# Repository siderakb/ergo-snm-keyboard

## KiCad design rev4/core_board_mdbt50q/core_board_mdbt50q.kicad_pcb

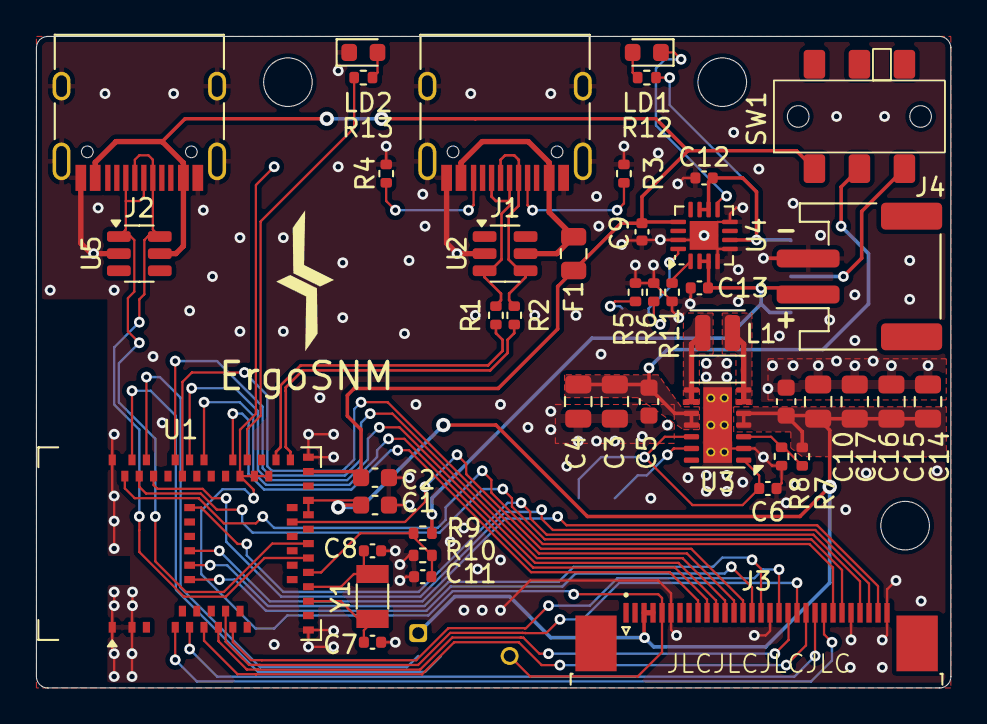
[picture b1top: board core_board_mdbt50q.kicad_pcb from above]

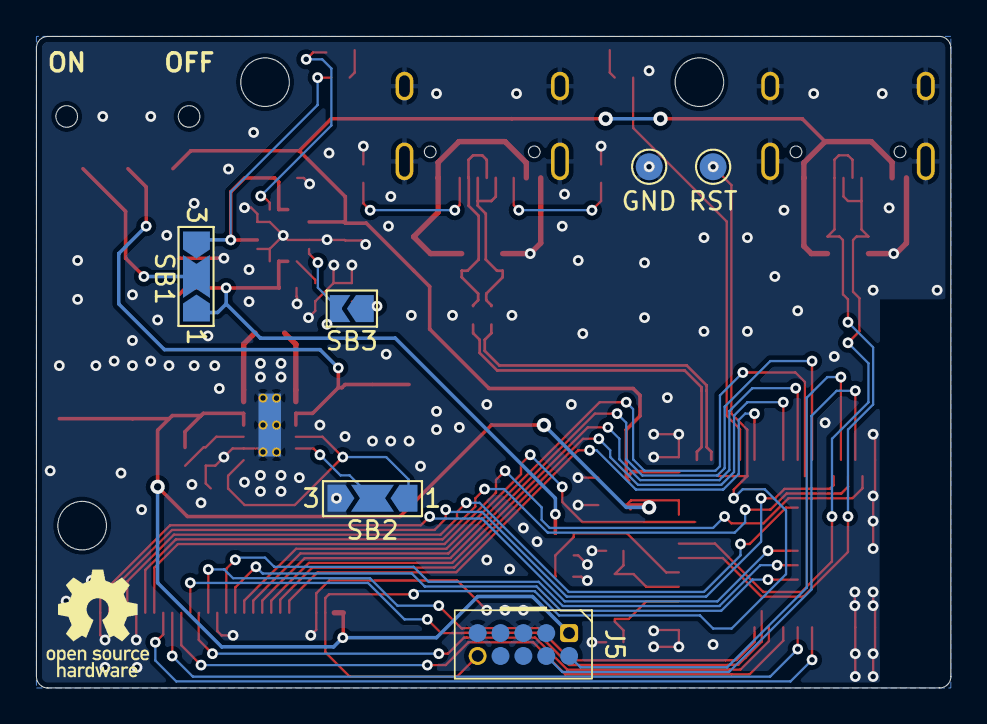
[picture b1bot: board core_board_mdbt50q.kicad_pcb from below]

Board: 2 copper layers, 50.8 x 36.2 mm, 54 parts (6 on the bottom side), 53 nets.

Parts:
C1, C2: 10uF; C_0603_1608Metric
C3, C4, C14, C15, C16, C17: 22uF; C_0805_2012Metric
C5, C10: 2.2uF; C_0603_1608Metric
C6, C11: 100nF; C_0402_1005Metric
C7, C8: 12pF; C_0402_1005Metric
C9: 1uF; C_0402_1005Metric
C12, C13: 4.7uF; C_0402_1005Metric
F1: 500mA, 6V; Fuse_0805_2012Metric
H1, H2, H3: MountingHole; MountingHole_2.7mm_M2.5_ISO7380
J1, J2: USB_C_Receptacle_USB2.0; USB_C_Receptacle_HRO_TYPE-C-31-M-12
J3: Conn_01x30; TE_3-1734839-0_1x30-1MP_P0.5mm_Horizontal
J4: Conn_Batt; JST_PH_S2B-PH-SM4-TB_1x02-1MP_P2.00mm_Horizontal
J5: Debug; SWD 10pin
L1: 1.5uH; L_Changjiang_FNR252012S
LD1: RED; LED_0603_1608Metric
LD2: BLUE; LED_0603_1608Metric
R1, R2: 27R; R_0402_1005Metric
R3, R4: 5.1k; R_0402_1005Metric
R5: 2k; R_0402_1005Metric
R6, R11, R12, R13: 10k; R_0402_1005Metric
R7: 1M; R_0402_1005Metric
R8: 180k; R_0402_1005Metric
R9: 820k; R_0402_1005Metric
R10: 2M; R_0402_1005Metric
SB1: Vsrc Select; SolderJumper-3_P2.0mm_Open_TrianglePad1.0x1.5mm_NumberLabels
SB2: Power Save; SolderJumper-3_P2.0mm_Open_TrianglePad1.0x1.5mm_NumberLabels
SB3: Charge Boost; SolderJumper-2_P1.3mm_Open_TrianglePad1.0x1.5mm
SW1: SW_DPDT_x2; MSKT-22D14-T
TP1: RST; TestPoint_Pad_D1.5mm
TP2: GND; TestPoint_Pad_D1.5mm
U1: MDBT50Q-1MV2; Raytac_MDBT50Q
U2, U5: SRV05-4; SOT-23-6
U3: TPS63020; VSON-14-1EP_3x4.45mm_P0.65mm_EP1.6x4.2mm_ThermalVias
U4: BQ24075RGT; VQFN-16-1EP_3x3mm_P0.5mm_EP1.6x1.6mm
Y1: 32.768kHz; Crystal_SMD_3215-2Pin_3.2x1.5mm

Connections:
+5V: F1.1, J1.A4 (VBUS), J1.A9 (VBUS), J1.B4 (VBUS), J1.B9 (VBUS), U2.5 (VP)
+BATT: C13.2, J4.1, R9.1, SB1.1 (A), U4.2 (BAT), U4.3 (BAT)
/MCU_D+: R2.2, U1.35 (D+)
/MCU_D-: R1.1, U1.34 (D-)
/PWR_SAVE: SB2.2 (C), U3.13 (PS/SYNC)
/VINA: C6.1, SB2.1 (A), U3.1 (VINA), U3.12 (EN)
GND: C1.2, C2.1, C3.2, C4.2, C5.2, C6.2, C7.1, C8.1, C9.2, C10.2, C11.2, C12.1, C13.1, C14.2, C15.2, C16.2, C17.2, J1.A1 (GND), J1.A12 (GND), J1.B1 (GND), J1.B12 (GND), J1.S1 (SHIELD), J2.A1 (GND), J2.A12 (GND), J2.B1 (GND), J2.B12 (GND), J2.S1 (SHIELD), J3.6, J3.17, J3.26, J3.30, J4.2, J5.3, J5.5, J5.9, LD2.1 (K), R3.2, R4.2, R5.2, R6.2, R8.2, R10.2, R11.1, SB2.3 (B), TP2.1, U1.1 (GND), U1.2 (GND), U1.15 (GND), U1.33 (GND), U1.55 (GND), U2.2 (VN), U3.2 (GND), U3.15 (PAD), U4.4 (~CE), U4.5 (EN2), U4.8 (VSS), U4.15 (SYSOFF), U4.17 (VSS), U5.2 (VN)
unnamed: J1.A5 (CC1), R3.1
unnamed: J1.B5 (CC2), R4.1
unnamed: L1.1, U3.8 (L1), U3.9 (L1)
unnamed: L1.2, U3.6 (L2), U3.7 (L2)
unnamed: LD1.2 (A), R12.2
unnamed: LD1.1 (K), U4.9 (~CHG)
unnamed: LD2.2 (A), R13.2
unnamed: SB1.2 (C), SW1.1 (A)
unnamed: R5.1, SB3.1 (A)
unnamed: R6.1, SB3.2 (B), U4.16 (ISET)
unnamed: C3.1, C4.1, C5.1, SW1.2 (B), U3.10 (VIN), U3.11 (VIN)
unnamed: R7.2, R8.1, U3.3 (FB)
unnamed: R11.2, U4.1 (TS)
P0.02: J3.20, U1.11 (P0.02)
P0.04: C11.1, R9.2, R10.1, U1.20 (P0.04)
P0.06: J2.A7 (D-), J2.B7 (D-), U1.22 (P0.06), U5.6 (IO4)
P0.08: J2.A6 (D+), J2.B6 (D+), U1.24 (P0.08), U5.1 (IO1)
P0.09: J3.25, U1.52 (P0.09)
P0.10: J3.24, U1.54 (P0.10)
P0.11: J3.14, U1.27 (P0.11)
P0.15: R13.1, U1.39 (P0.15)
P0.17: J3.9, U1.41 (P0.17)
P0.20: J3.10, U1.44 (P0.20)
P0.22: J3.11, U1.46 (P0.22)
P0.24: J3.12, U1.48 (P0.24)
P0.29: J3.19, U1.10 (P0.29)
P0.31: J3.18, U1.12 (P0.31)
P1.00: J3.13, U1.47 (P1.00)
P1.01: J3.27, U1.61 (P1.01)
P1.02: J3.28, U1.50 (P1.02)
P1.04: J3.15, U1.56 (P1.04)
P1.06: J3.16, U1.57 (P1.06)
P1.07: J3.29, U1.58 (P1.07)
P1.11: J3.23, U1.4 (P1.11)
P1.13: J3.22, U1.6 (P1.13)
P1.15: J3.21, U1.8 (P1.15)
RESET: J3.5, J5.10, TP1.1, U1.36 (P0.14), U1.38 (P0.16), U1.40 (P0.18)
SWC: J5.4, U1.53 (SWDCLK)
SWD: J5.2, U1.51 (SWDIO)
USB_D+: J1.A6 (D+), J1.B6 (D+), R2.1, U2.3 (IO2)
USB_D-: J1.A7 (D-), J1.B7 (D-), R1.2, U2.4 (IO3)
VBUS: C2.2, C9.1, F1.2, J2.A4 (VBUS), J2.A9 (VBUS), J2.B4 (VBUS), J2.B9 (VBUS), SW1.3 (C), U1.32 (VBUS), U4.13 (IN), U5.5 (VP)
VDD: C1.1, C10.1, C14.1, C15.1, C16.1, C17.1, J3.3, J3.4, J5.1, R7.1, U1.28 (VDD), U1.30 (VDDH), U3.4 (VOUT), U3.5 (VOUT)
VDDH: C12.2, R12.1, SB1.3 (B), U4.6 (EN1), U4.10 (OUT), U4.11 (OUT)
XL1: C7.2, U1.17 (P0.00), Y1.2
XL2: C8.2, U1.18 (P0.01), Y1.1

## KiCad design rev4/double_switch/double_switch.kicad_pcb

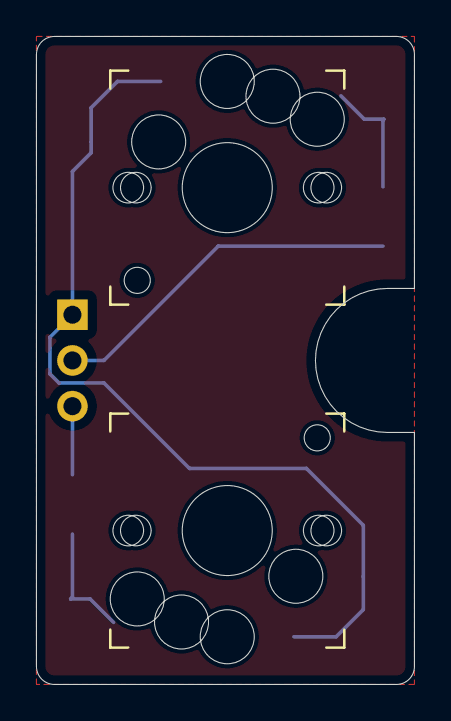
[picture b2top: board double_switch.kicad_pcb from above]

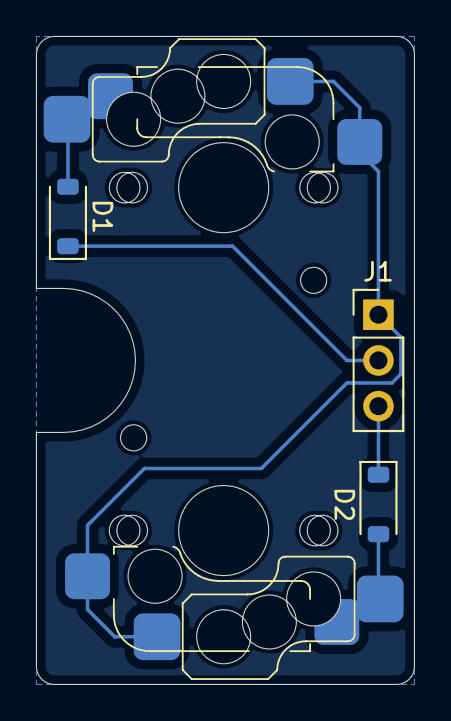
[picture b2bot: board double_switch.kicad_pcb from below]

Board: 2 copper layers, 21.0 x 36.0 mm, 5 parts (3 on the bottom side), 5 nets.

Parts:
D1, D2: 1N4148; D_SOD-123
J1: Conn_01x03; PinHeader_1x03_P2.54mm_Vertical
SW1, SW2: SW_Push_45deg; SW_MX_Kailh_Choc_V1V2_HotSwap_Hybrid_alt1

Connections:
COL0: J1.1, SW1.1, SW2.1
unnamed: D1.2 (A), SW1.2
unnamed: D2.2 (A), SW2.2
ROW0: D1.1 (K), J1.2
ROW1: D2.1 (K), J1.3

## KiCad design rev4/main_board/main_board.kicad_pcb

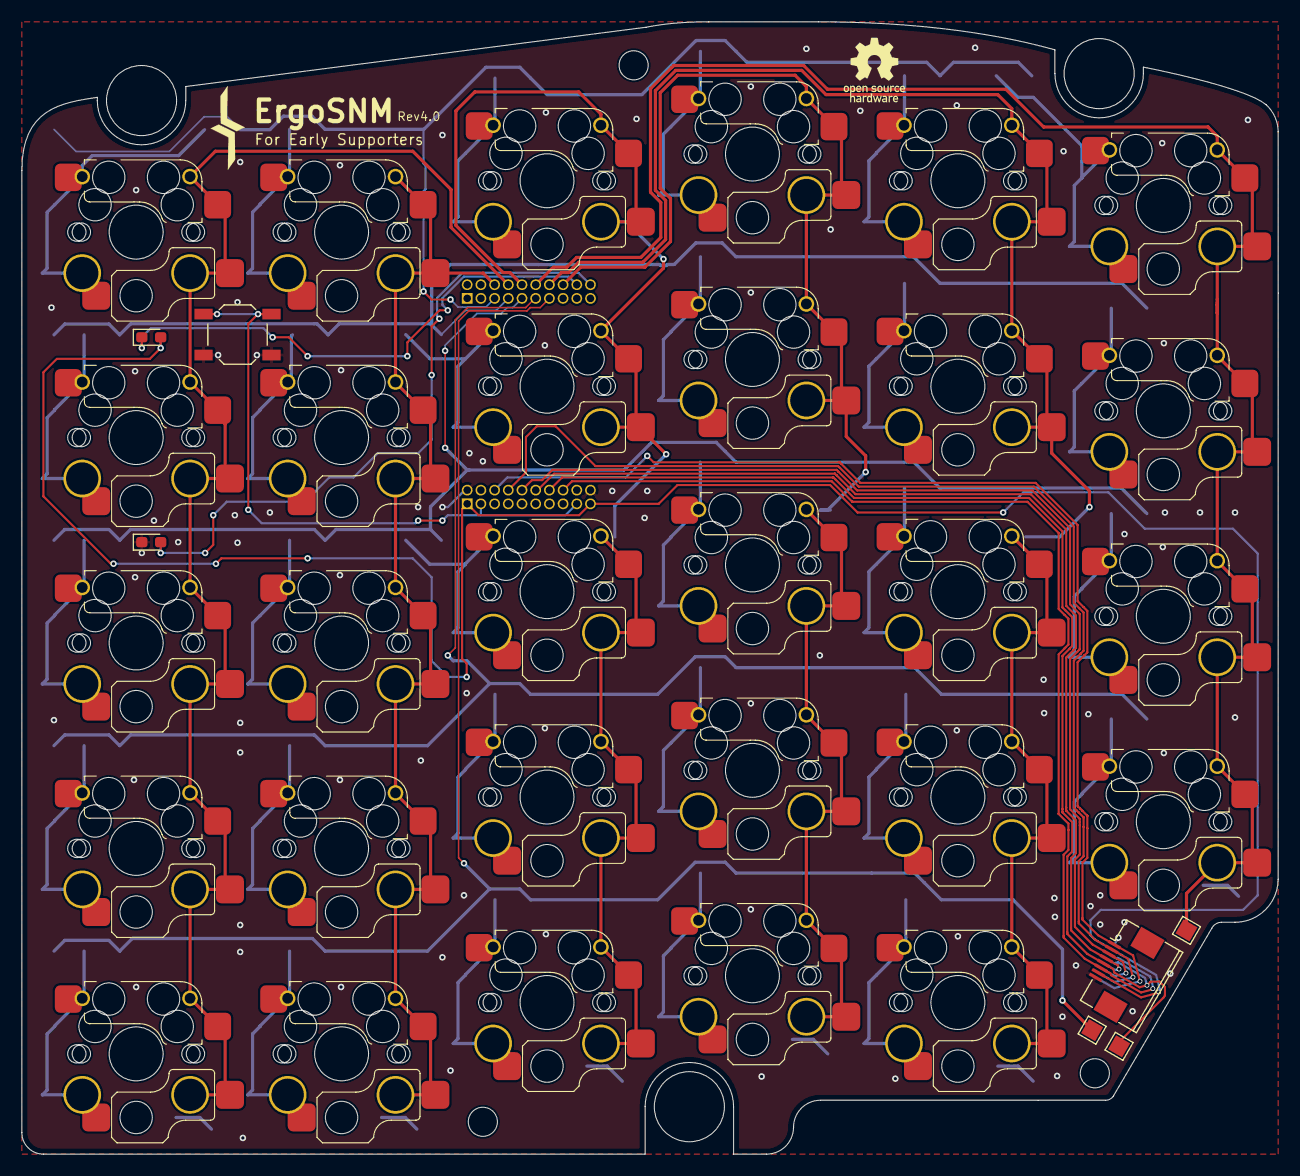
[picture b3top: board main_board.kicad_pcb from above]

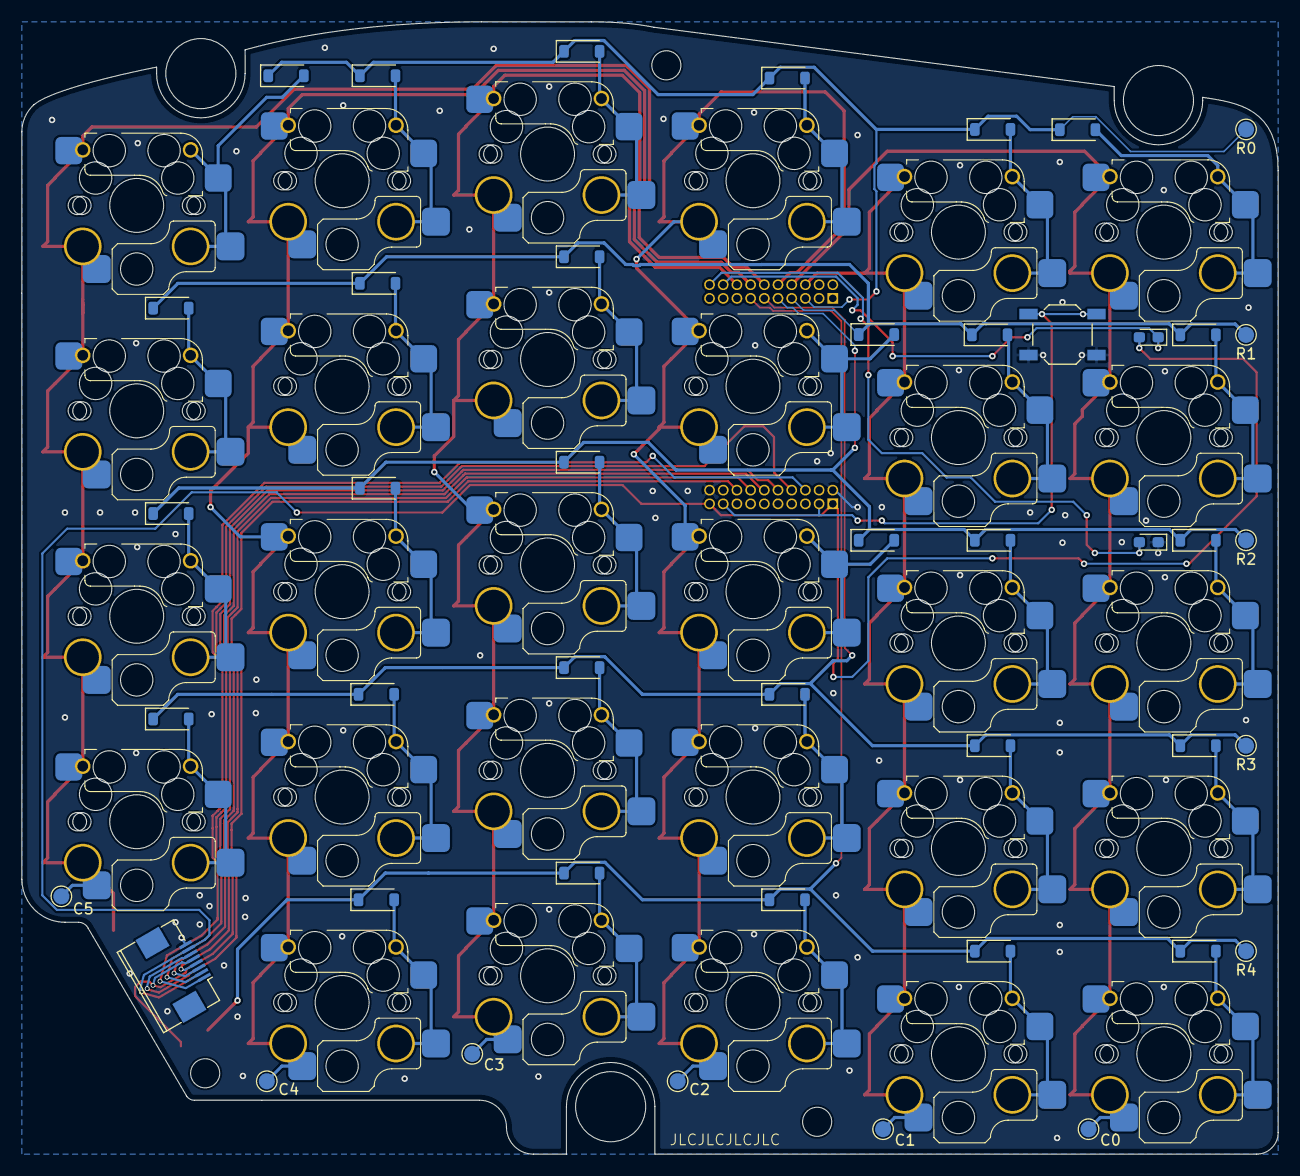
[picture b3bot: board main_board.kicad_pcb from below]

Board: 2 copper layers, 116.5 x 105.0 mm, 88 parts (48 on the bottom side), 51 nets.

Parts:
D1, D2, D3, D4, D5, D6, D7, D8, D9, D10, D11, D12, D13, D14, D15, D16, D17, D18, D19, D20, D21, D22, D23, D24, D25, D26, D27, D28, D29: 1N4148; D_SOD-123
H1, H8, H10: MountingHole_2.7mm_M2.5_ISO14580
H2, H3, H7: mounting_hole_6.5mm
J1, J3: Conn_MouseSensor; FPC_8P_0.5mm_AFC01-S08FCA-00
J4, J5: Conn_02x10_Odd_Even; PinSocket_2x10_P1.27mm_Vertical
KEY1, KEY2, KEY3, KEY4, KEY5, KEY6, KEY7, KEY8, KEY9, KEY10, KEY11, KEY12, KEY13, KEY14, KEY15, KEY16, KEY17, KEY18, KEY19, KEY20, KEY21, KEY22, KEY23, KEY24, KEY25, KEY26, KEY27, KEY28, KEY29: SW_Push_45deg; SW_MX_Kailh_Choc_V1V2_HotSwap_Hybrid_double
LD1, LD2, LD3, LD4: LED; LED_0603_1608Metric_Pad1.05x0.95mm_HandSolder
SW2, SW3: RESET; SW_SPST_TL3342
TP1: R0; TestPoint_Pad_D1.5mm
TP2: R1; TestPoint_Pad_D1.5mm
TP3: R2; TestPoint_Pad_D1.5mm
TP4: R3; TestPoint_Pad_D1.5mm
TP5: R4; TestPoint_Pad_D1.5mm
TP6: C0; TestPoint_Pad_D1.5mm
TP7: C1; TestPoint_Pad_D1.5mm
TP8: C2; TestPoint_Pad_D1.5mm
TP9: C3; TestPoint_Pad_D1.5mm
TP10: C4; TestPoint_Pad_D1.5mm
TP11: C5; TestPoint_Pad_D1.5mm
TP12, TP13, TP14: TestPoint; TestPoint_Pad_1.5x1.5mm

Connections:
COL_0: J5.8, KEY1.1, KEY7.1, KEY13.1, KEY19.1, KEY25.1, TP6.1
COL_1: J5.6, KEY2.1, KEY8.1, KEY14.1, KEY20.1, KEY26.1, TP7.1
COL_2: J5.10, KEY3.1, KEY9.1, KEY15.1, KEY21.1, KEY27.1, TP8.1
COL_3: J5.16, KEY4.1, KEY10.1, KEY16.1, KEY22.1, KEY28.1, TP9.1
COL_4: J5.14, KEY5.1, KEY11.1, KEY17.1, KEY23.1, KEY29.1, TP10.1
COL_5: J5.12, KEY6.1, KEY12.1, KEY18.1, KEY24.1, TP11.1, TP13.1
GND: J1.8, J3.8, J4.2, J4.20, LD2.1 (K), LD3.1 (K), SW2.1, SW3.1
IO_0: J1.1, J3.1, J4.6
LED_CHG: J5.18, LD1.1 (K), LD4.1 (K)
LED_STA: J5.20, LD2.2 (A), LD3.2 (A)
MISO: J1.5, J3.5, J4.14, TP12.1
MOSI: J1.4, J3.4, J4.12
MOTION: J1.2, J3.2, J4.8
unnamed: D1.2 (A), KEY1.2
unnamed: D2.2 (A), KEY2.2
unnamed: D3.2 (A), KEY3.2
unnamed: D4.2 (A), KEY4.2
unnamed: D5.2 (A), KEY5.2
unnamed: D6.2 (A), KEY6.2
unnamed: D7.2 (A), KEY7.2
unnamed: D8.2 (A), KEY8.2
unnamed: D9.2 (A), KEY9.2
unnamed: D10.2 (A), KEY10.2
unnamed: D11.2 (A), KEY11.2
unnamed: D12.2 (A), KEY12.2
unnamed: D13.2 (A), KEY13.2
unnamed: D14.2 (A), KEY14.2
unnamed: D15.2 (A), KEY15.2
unnamed: D16.2 (A), KEY16.2
unnamed: D17.2 (A), KEY17.2
unnamed: D18.2 (A), KEY18.2
unnamed: D19.2 (A), KEY19.2
unnamed: D20.2 (A), KEY20.2
unnamed: D21.2 (A), KEY21.2
unnamed: D22.2 (A), KEY22.2
unnamed: D23.2 (A), KEY23.2
unnamed: D24.2 (A), KEY24.2
unnamed: D25.2 (A), KEY25.2
unnamed: D26.2 (A), KEY26.2
unnamed: D27.2 (A), KEY27.2
unnamed: D28.2 (A), KEY28.2
unnamed: D29.2 (A), KEY29.2
RESET: J4.3, J4.17, SW2.2, SW3.2
ROW_0: D1.1 (K), D2.1 (K), D3.1 (K), D4.1 (K), D5.1 (K), D6.1 (K), J5.5, TP1.1
ROW_1: D7.1 (K), D8.1 (K), D9.1 (K), D10.1 (K), D11.1 (K), D12.1 (K), J5.7, TP2.1
ROW_2: D13.1 (K), D14.1 (K), D15.1 (K), D16.1 (K), D17.1 (K), D18.1 (K), J5.9, TP3.1
ROW_3: D19.1 (K), D20.1 (K), D21.1 (K), D22.1 (K), D23.1 (K), D24.1 (K), J5.11, TP4.1
ROW_4: D25.1 (K), D26.1 (K), D27.1 (K), D28.1 (K), D29.1 (K), J5.13, TP5.1, TP14.1
SCLK: J1.3, J3.3, J4.10
VDD: J1.7, J3.7, J4.1, J4.19, LD1.2 (A), LD4.2 (A)
nCS: J1.6, J3.6, J4.16

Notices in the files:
rev4/main_board/main_board.kicad_pcb:
Open source hardware, CERN-OHL-P v2
